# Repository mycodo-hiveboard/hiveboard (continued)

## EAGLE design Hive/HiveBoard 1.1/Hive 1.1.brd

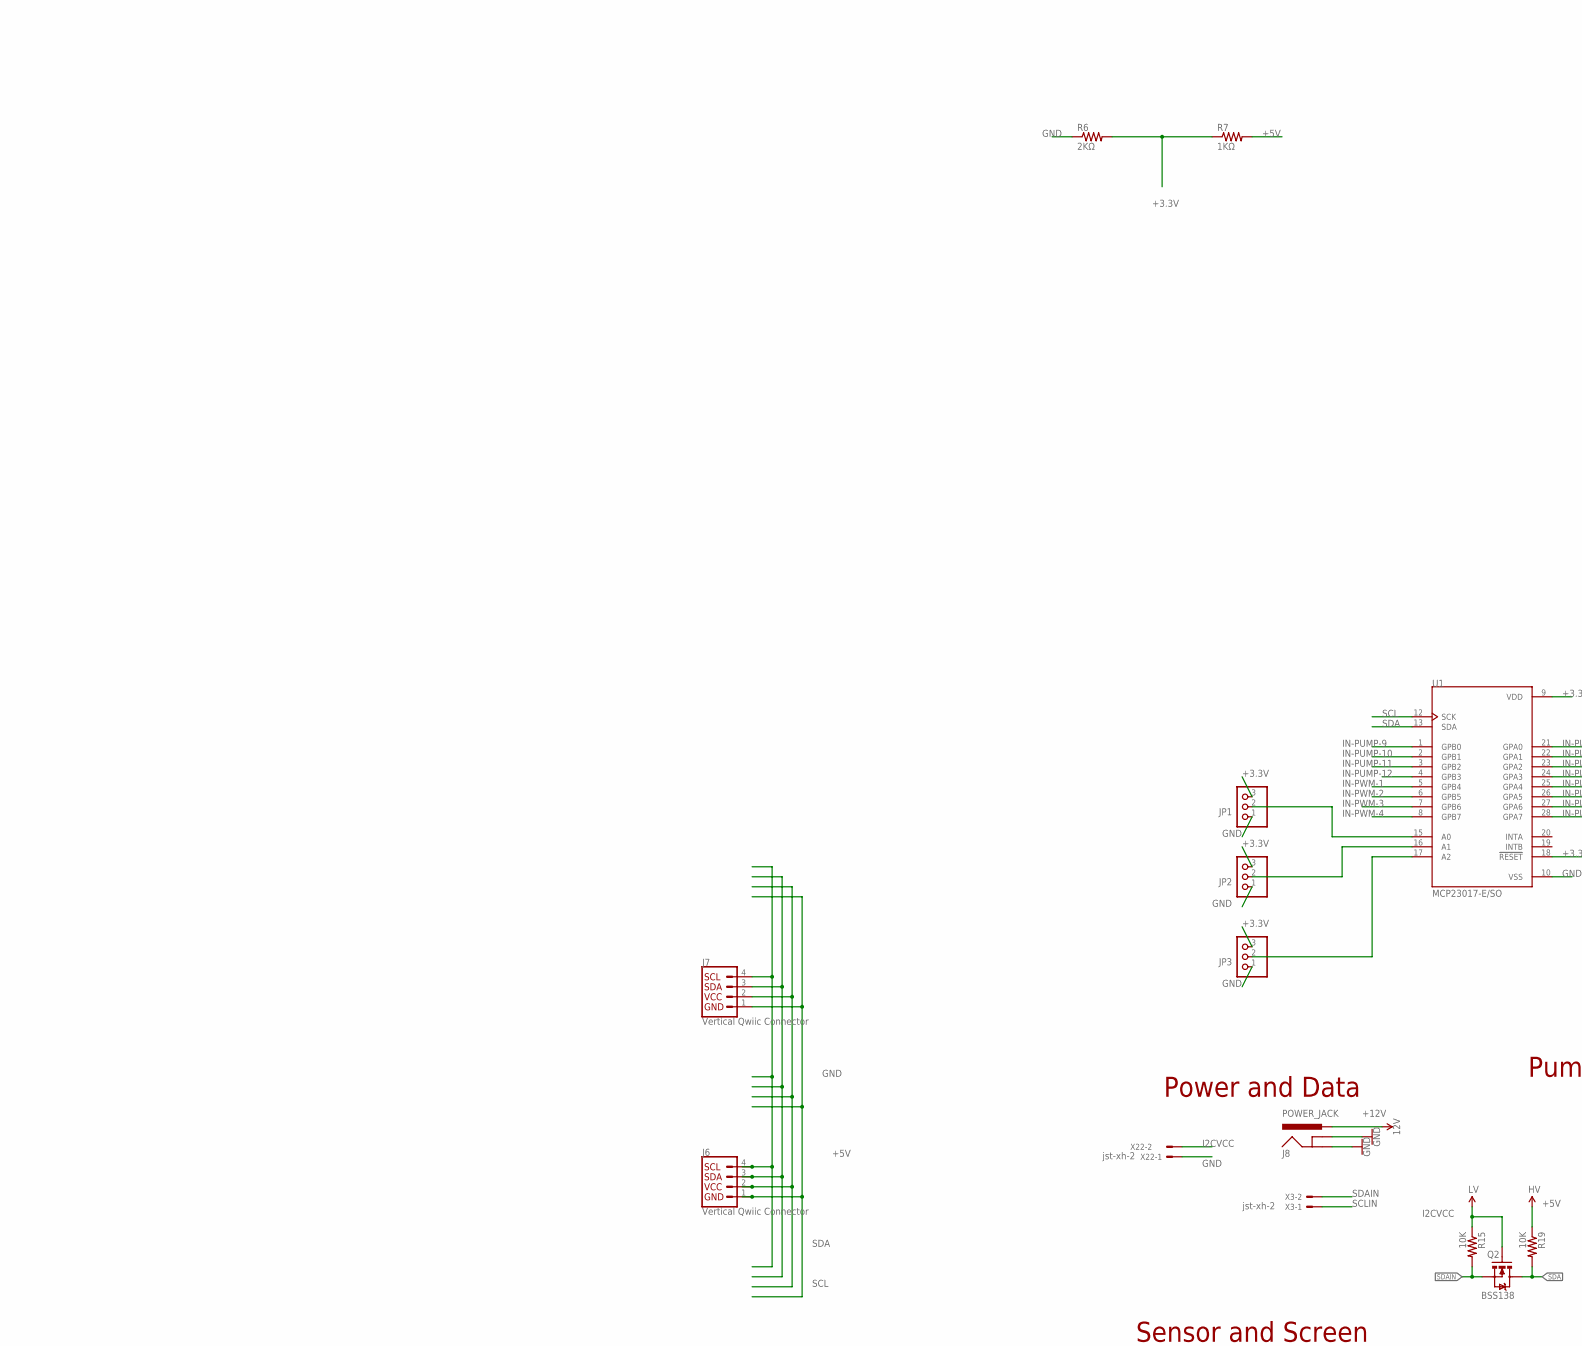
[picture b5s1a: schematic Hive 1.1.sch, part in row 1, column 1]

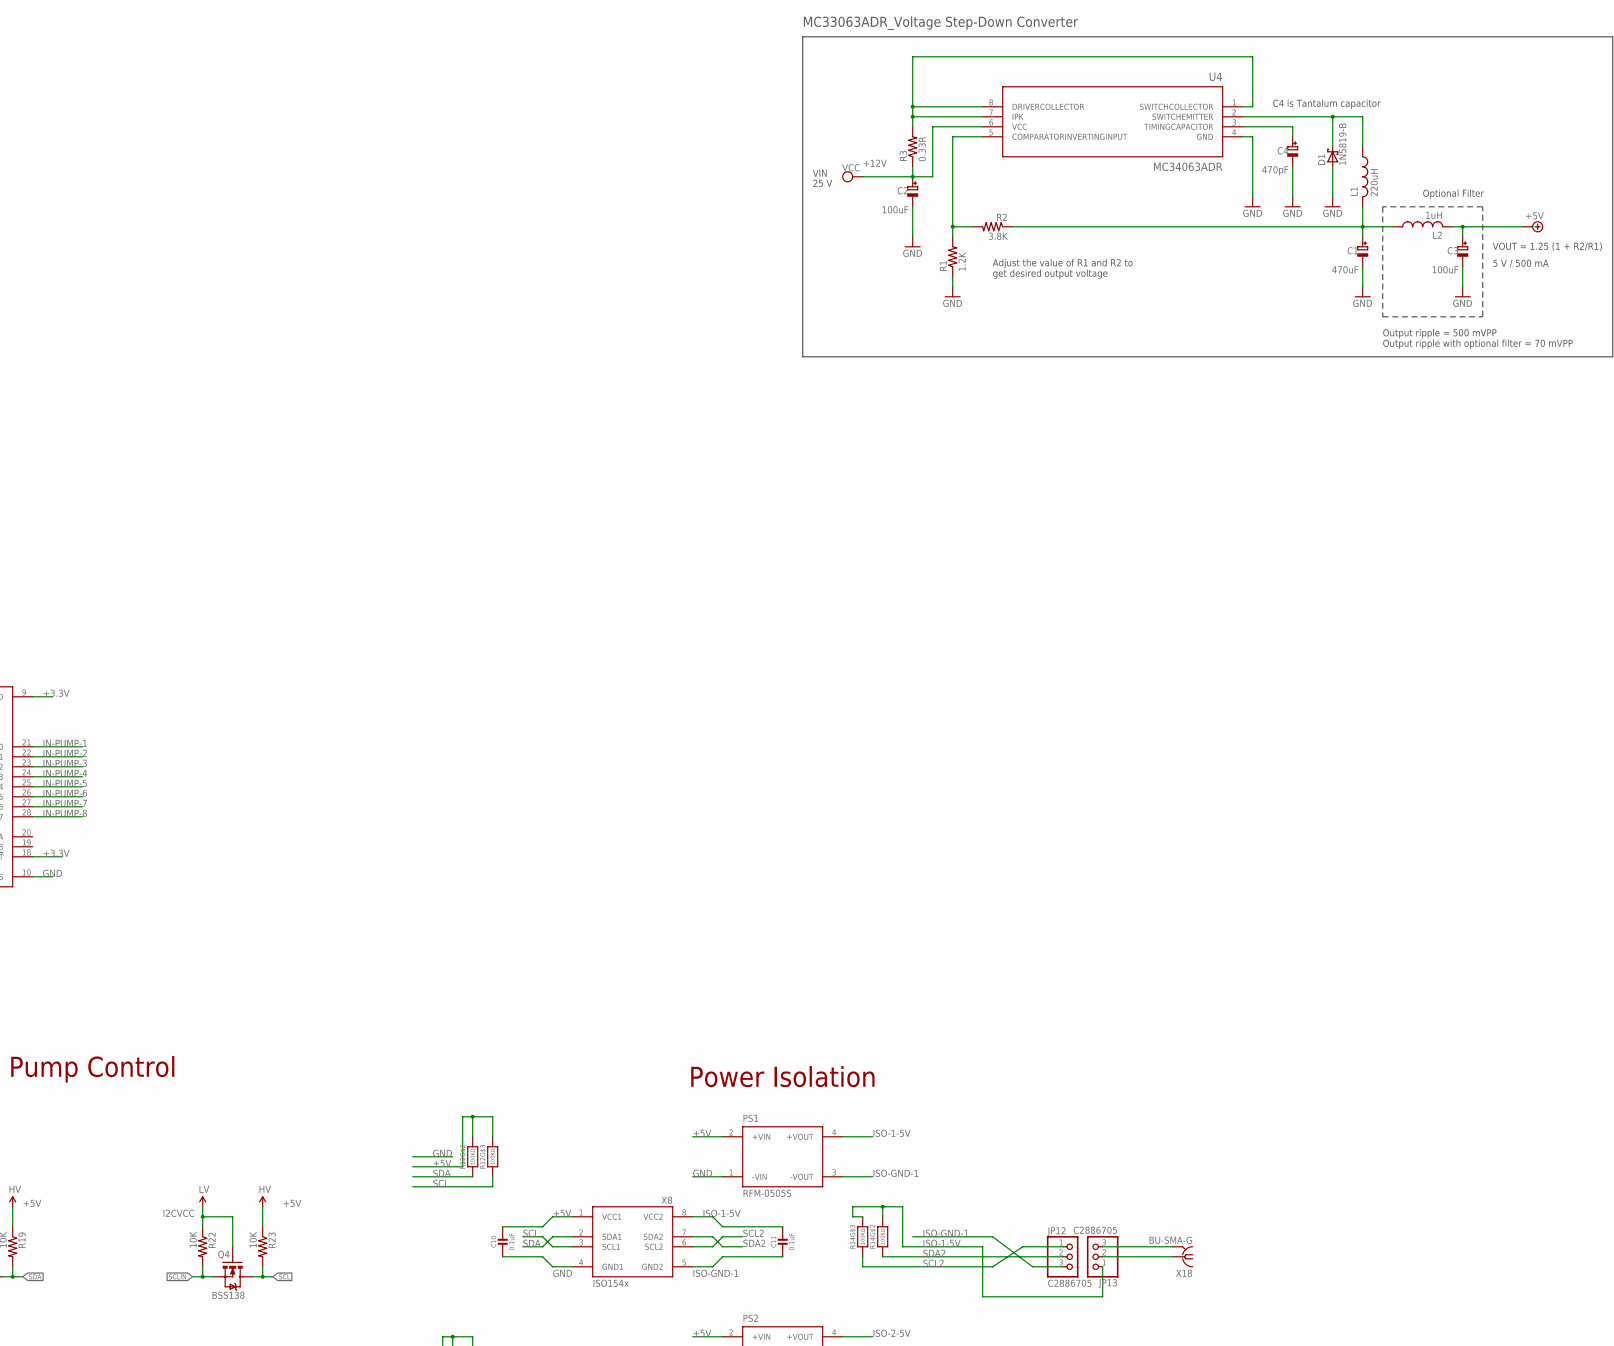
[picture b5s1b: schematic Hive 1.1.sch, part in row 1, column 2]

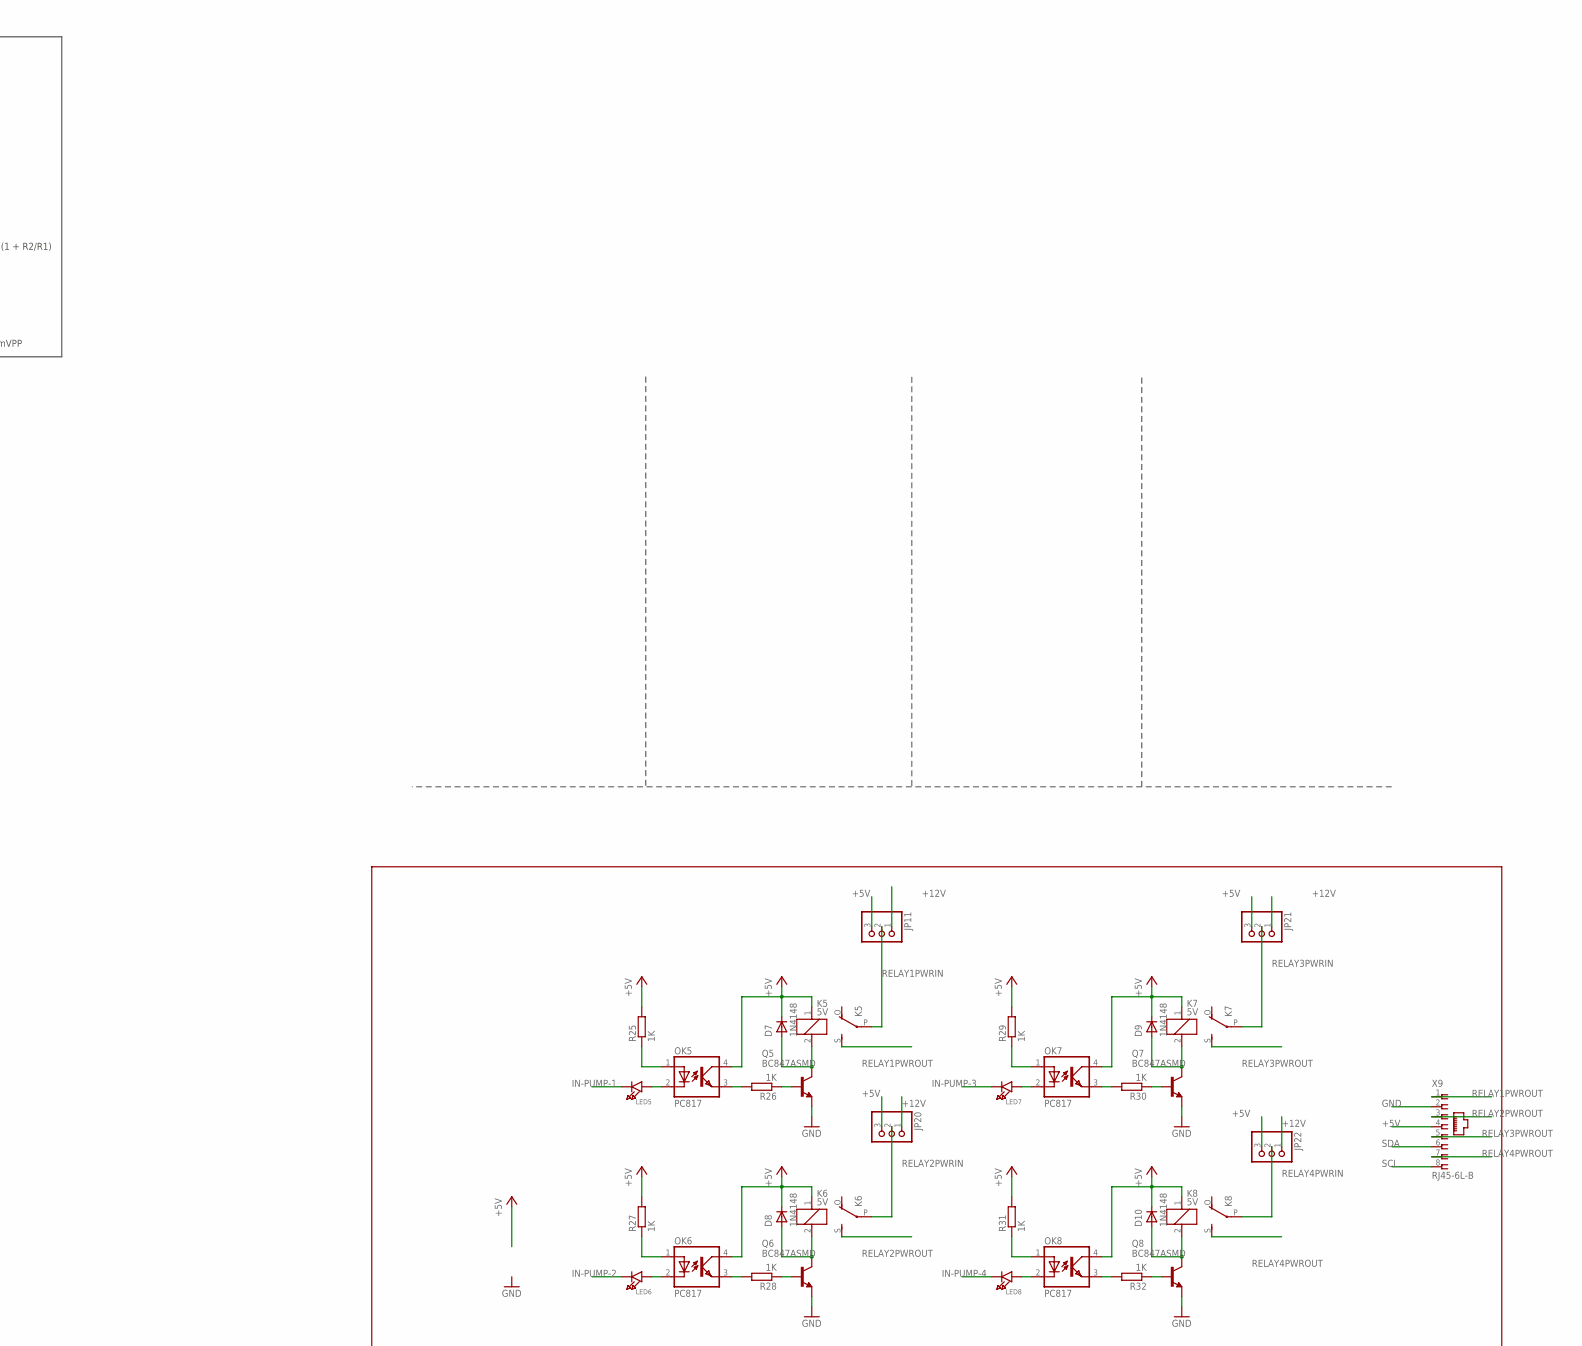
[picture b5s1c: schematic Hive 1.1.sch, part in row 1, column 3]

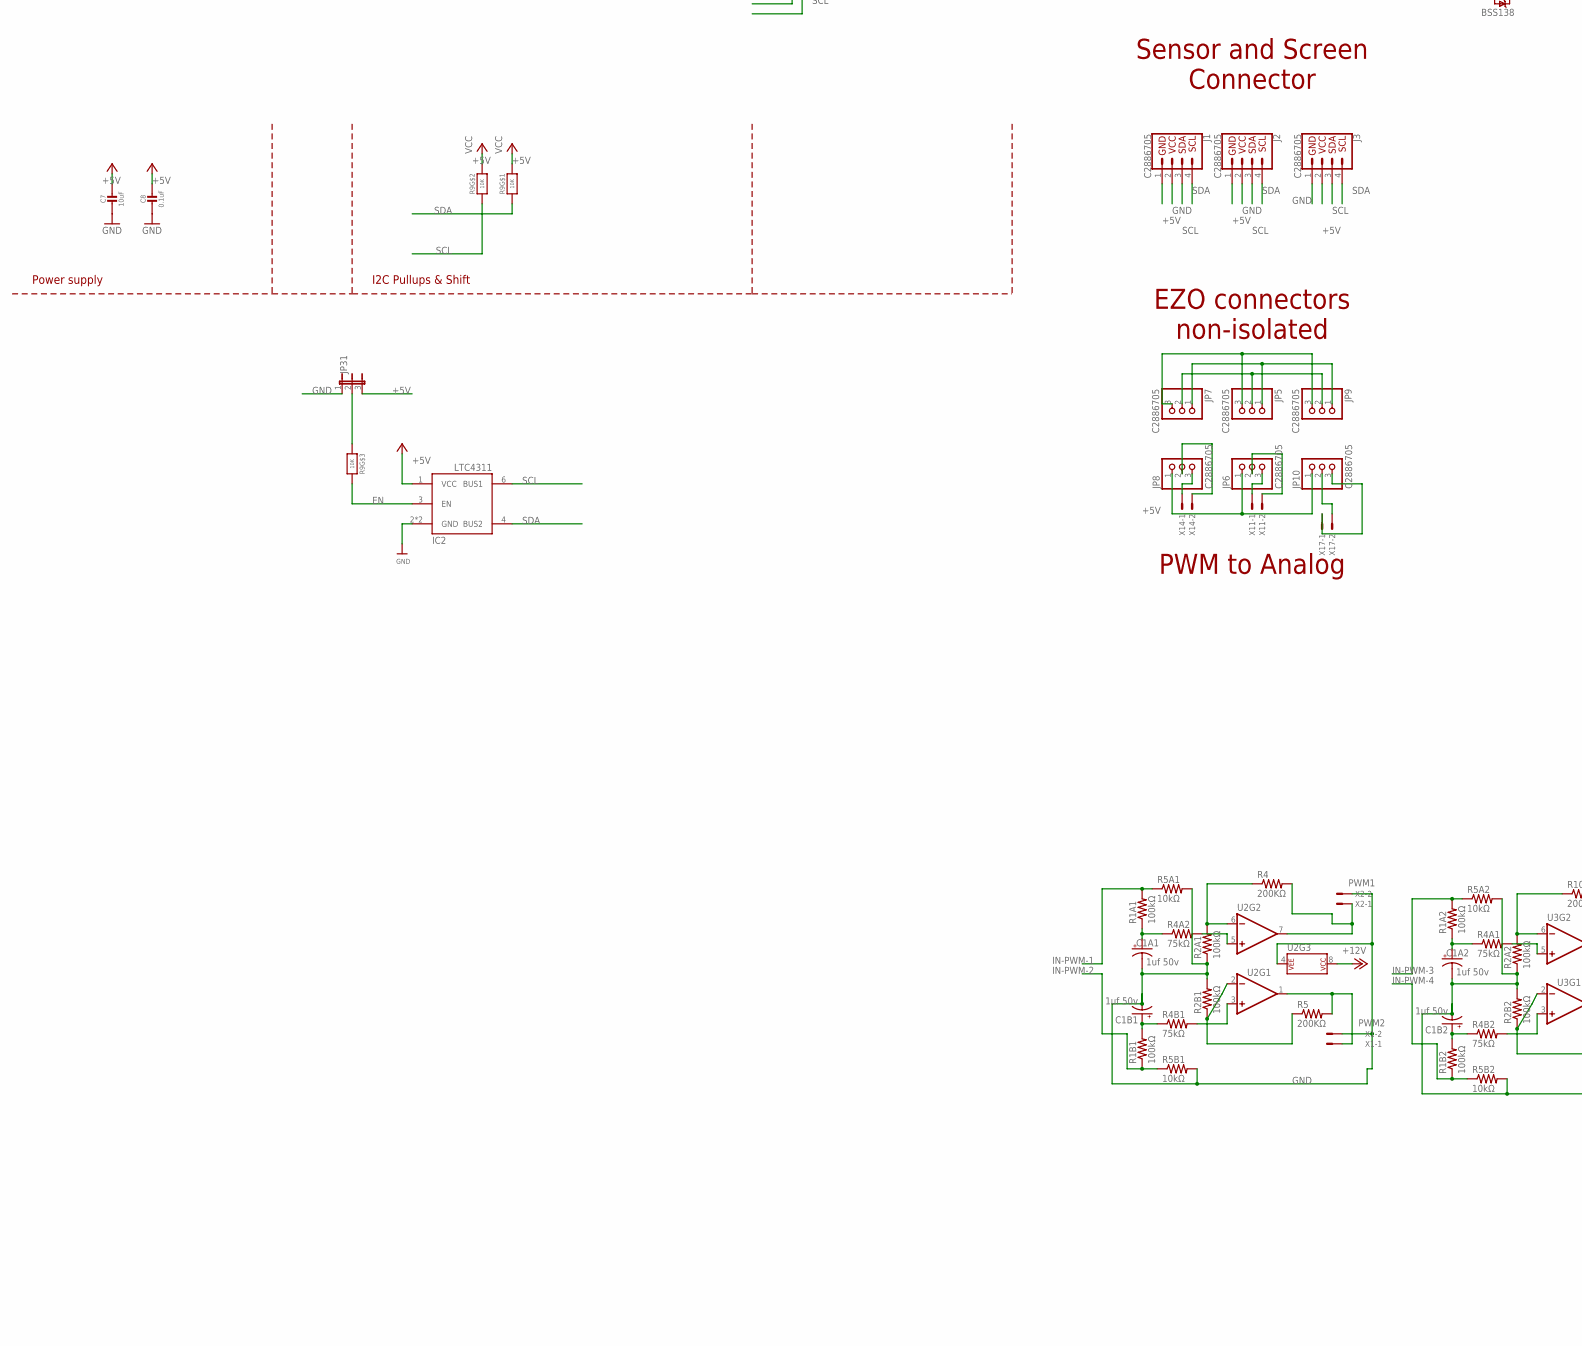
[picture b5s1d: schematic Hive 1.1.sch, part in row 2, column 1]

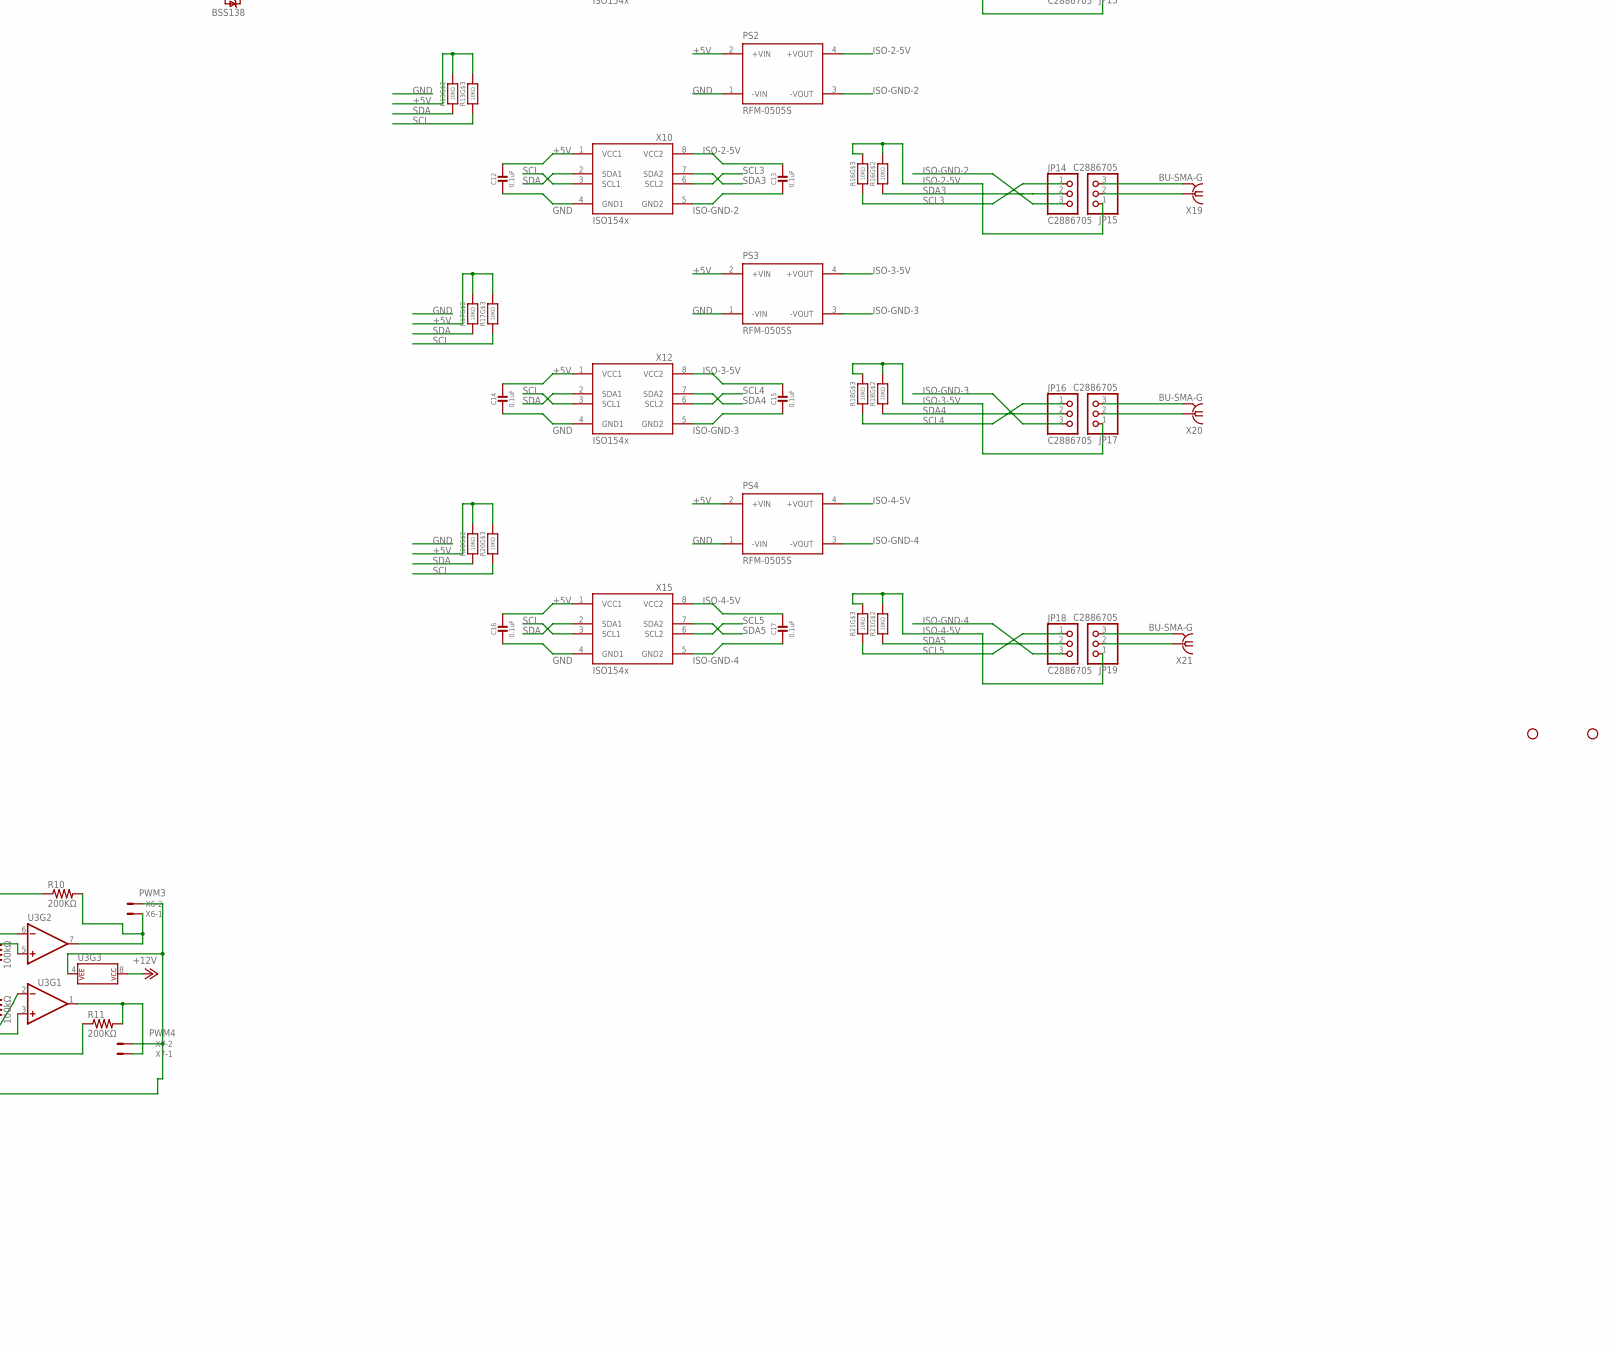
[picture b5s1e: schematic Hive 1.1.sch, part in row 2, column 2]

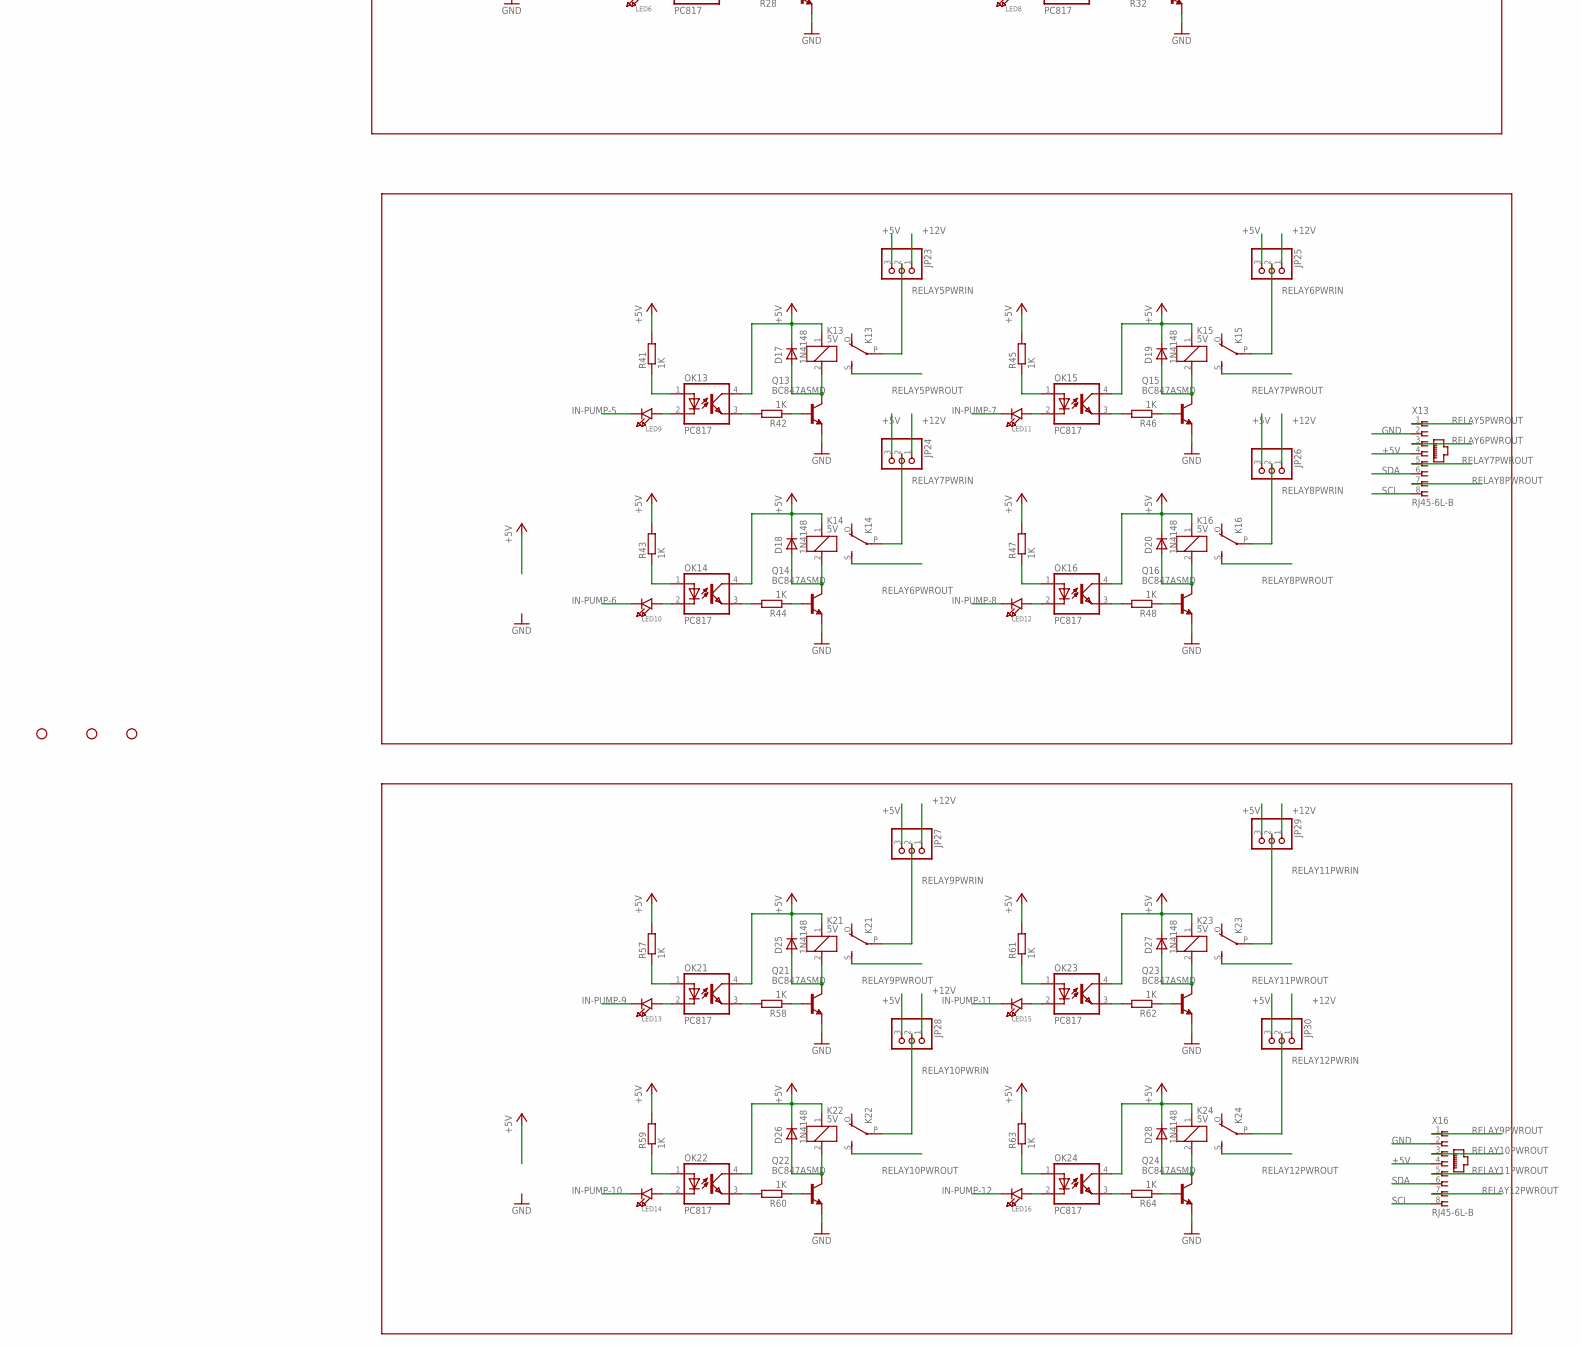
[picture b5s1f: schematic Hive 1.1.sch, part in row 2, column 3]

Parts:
C1: 470uF; PANASONIC_C
C1A1, C1A2, C1B1, C1B2: 1uf 50v; UD-4X5,8_NICHICON
C2, C3: 100uF; PANASONIC_C
C4: 470pF; PANASONIC_C
C7: 10uF; 0805-NO
C8, C10, C11, C12, C13, C14, C15, C16, C17: 0.1uF; 0603-NO
D1: 1N5819-B; DO41-7.6
D7, D8, D9, D10, D17, D18, D19, D20, D25, D26, D27, D28: 1N4148; SMA-DO214AC
H1, H2, H3, H4: STAND-OFF
IC2: LTC4311_SC70; SC70-6L
J1, J2, J3: C2886705; 1X04
J6, J7: Vertical Qwiic Connector; JST04_1MM_VERT
J8: POWER_JACK; POWER_JACK_PTH
JP1, JP2, JP3: HEADER-1X3ROUND; 1X03_ROUND
JP5, JP6, JP7, JP8, JP9, JP10, JP12, JP13, JP14, JP15, JP16, JP17, JP18, JP19: C2886705; 1X03-CLEANBIG
JP11, JP20, JP21, JP22, JP23, JP24, JP25, JP26, JP27, JP28, JP29, JP30: PINHD-1X3; 1X03
JP31: JUMPER3
K5, K6, K7, K8, K13, K14, K15, K16, K21, K22, K23, K24: 5V; ZF112
L1: 220uH; L3216C
L2: 1uH; L3216C
LED5, LED6, LED7, LED8, LED9, LED10, LED11, LED12, LED13, LED14, LED15, LED16: LED0603; CHIPLED_0603
OK5, OK6, OK7, OK8, OK13, OK14, OK15, OK16, OK21, OK22, OK23, OK24: PC817; DIL04
PS1, PS2, PS3, PS4: RFM-0505S; CONV_RFM-0505S
Q2, Q4: BSS138; SOT23-3
Q5, Q6, Q7, Q8, Q13, Q14, Q15, Q16, Q21, Q22, Q23, Q24: BC847ASMD; SOT23
R1: 1.2K; M0805
R1A1, R1A2, R1B1, R1B2, R2A1, R2A2, R2B1, R2B2: 100kΩ; M1206
R2: 3.8K; M0805
R3: 0.33R; M0805
R4, R5, R10, R11: 200KΩ; R0402
R4A1, R4A2, R4B1, R4B2: 75kΩ; M1206
R5A1, R5A2, R5B1, R5B2: 10kΩ; M1206
R6: 2KΩ; R1206
R7: 1KΩ; R1206
R9: 10K; RESPACK_4X0603
R12, R14: 100KΩ; RESPACK_4X0603
R13, R16, R17, R18, R20, R21: 10KΩ; RESPACK_4X0603
R15, R19, R22, R23: 10K; 0603-RES
R25, R26, R27, R28, R29, R30, R31, R32, R41, R42, R43, R44, R45, R46, R47, R48, R57, R58, R59, R60, R61, R62, R63, R64: 1K; R1206
U1: MCP23017-E/SO; SOIC127P1030X265-28N
U2, U3: LM358; SO08
U4: MC34063ADR; D8
X1: PWM2; JST-XH-02-PACKAGE-LONG-PAD
X2: PWM1; JST-XH-02-PACKAGE-LONG-PAD
X3, X11, X14, X17, X22: jst-xh-2; JST-XH-02-PACKAGE-LONG-PAD
X6: PWM3; JST-XH-02-PACKAGE-LONG-PAD
X7: PWM4; JST-XH-02-PACKAGE-LONG-PAD
X8, X10, X12, X15: ISO154X; SOIC8_150MIL
X9, X13, X16: RJ45-6L-B; RJ45-NO-SHIELD
X18, X19, X20, X21: BU-SMA-G

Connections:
+3.3V: JP1.3, JP2.3, JP3.3, R6.2, R7.1, U1.9 (VDD), U1.18 (!RESET)
+5V: C3.+, C7.1, C8.1, C10.1, C12.1, C14.1, C16.1, D7.K (C), D8.K (C), D9.K (C), D10.K (C), D17.K (C), D18.K (C), D19.K (C), D20.K (C), D25.K (C), D26.K (C), D27.K (C), D28.K (C), IC2.1 (VCC), J1.1, J2.1, J3.2, J6.3, J7.3, JP6.1, JP8.1, JP10.1, JP11.3, JP20.3, JP21.3, JP22.3, JP23.3, JP24.3, JP25.3, JP26.3, JP27.3, JP28.3, JP29.3, JP30.3, JP31.3, K5.1, K6.1, K7.1, K8.1, K13.1, K14.1, K15.1, K16.1, K21.1, K22.1, K23.1, K24.1, L2.2, OK5.4 (COL), OK6.4 (COL), OK7.4 (COL), OK8.4 (COL), OK13.4 (COL), OK14.4 (COL), OK15.4 (COL), OK16.4 (COL), OK21.4 (COL), OK22.4 (COL), OK23.4 (COL), OK24.4 (COL), PS1.2 (+VIN), PS2.2 (+VIN), PS3.2 (+VIN), PS4.2 (+VIN), R7.2, R9.7 (2), R9.8 (2), R12.6 (2), R12.7 (2), R13.6 (2), R13.7 (2), R17.6 (2), R17.7 (2), R19.1, R20.6 (2), R20.7 (2), R23.1, R25.2, R27.2, R29.2, R31.2, R41.2, R43.2, R45.2, R47.2, R57.2, R59.2, R61.2, R63.2, X8.1 (VCC1), X9.4, X10.1 (VCC1), X12.1 (VCC1), X13.4, X15.1 (VCC1), X16.4
+12V: C2.+, J8.PWR, JP11.1, JP20.1, JP21.1, JP22.1, JP23.1, JP24.1, JP25.1, JP26.1, JP27.1, JP28.1, JP29.1, JP30.1, R3.1, U2.8 (P$V+), U3.8 (P$V+), U4.6 (VCC)
EN: IC2.3 (EN), R9.6 (2)
GND: C1.-, C1A1.-, C1A2.-, C1B1.-, C1B2.-, C2.-, C3.-, C4.-, C7.2, C8.2, C10.2, C12.2, C14.2, C16.2, D1.A, IC2.2 (GND), IC2.5 (GND), J1.2, J2.2, J3.1, J6.4, J7.4, J8.GND, J8.GNDBREAK, JP1.1, JP2.1, JP3.1, JP5.3, JP7.3, JP9.3, JP31.1, PS1.1 (-VIN), PS2.1 (-VIN), PS3.1 (-VIN), PS4.1 (-VIN), Q5.2 (E), Q6.2 (E), Q7.2 (E), Q8.2 (E), Q13.2 (E), Q14.2 (E), Q15.2 (E), Q16.2 (E), Q21.2 (E), Q22.2 (E), Q23.2 (E), Q24.2 (E), R1.1, R2A1.1, R2A2.1, R2B1.2, R2B2.2, R5A1.2, R5A2.2, R5B1.2, R5B2.2, R6.1, U1.10 (VSS), U2.4 (P$V-), U3.4 (P$V-), U4.4 (GND), X1.2, X2.2, X6.2, X7.2, X8.4 (GND1), X9.2, X10.4 (GND1), X12.4 (GND1), X13.2, X15.4 (GND1), X16.2, X22.1
I2CVCC: Q2.1 (G), Q4.1 (G), R15.1, R22.1, X22.2
IN-PUMP-1: LED5.C, U1.21 (GPA0)
IN-PUMP-2: LED6.C, U1.22 (GPA1)
IN-PUMP-3: LED7.C, U1.23 (GPA2)
IN-PUMP-4: LED8.C, U1.24 (GPA3)
IN-PUMP-5: LED9.C, U1.25 (GPA4)
IN-PUMP-6: LED10.C, U1.26 (GPA5)
IN-PUMP-7: LED11.C, U1.27 (GPA6)
IN-PUMP-8: LED12.C, U1.28 (GPA7)
IN-PUMP-9: LED13.C, U1.1 (GPB0)
IN-PUMP-10: LED14.C, U1.2 (GPB1)
IN-PUMP-11: LED15.C, U1.3 (GPB2)
IN-PUMP-12: LED16.C, U1.4 (GPB3)
IN-PWM-1: R1A1.2, R5A1.1, U1.5 (GPB4)
IN-PWM-2: R1B1.1, R5B1.1, U1.6 (GPB5)
IN-PWM-3: R1A2.2, R5A2.1, U1.7 (GPB6)
IN-PWM-4: R1B2.1, R5B2.1, U1.8 (GPB7)
ISO-1-5V: C11.1, JP13.1, PS1.4 (+VOUT), R14.6 (2), R14.7 (2), X8.8 (VCC2)
ISO-2-5V: C13.1, JP15.1, PS2.4 (+VOUT), R16.6 (2), R16.7 (2), X10.8 (VCC2)
ISO-3-5V: C15.1, JP17.1, PS3.4 (+VOUT), R18.6 (2), R18.7 (2), X12.8 (VCC2)
ISO-4-5V: C17.1, JP19.1, PS4.4 (+VOUT), R21.6 (2), R21.7 (2), X15.8 (VCC2)
ISO-GND-1: C11.2, JP12.3, PS1.3 (-VOUT), X8.5 (GND2)
ISO-GND-2: C13.2, JP14.3, PS2.3 (-VOUT), X10.5 (GND2)
ISO-GND-3: C15.2, JP16.3, PS3.3 (-VOUT), X12.5 (GND2)
ISO-GND-4: C17.2, JP18.3, PS4.3 (-VOUT), X15.5 (GND2)
ISO-PRB-1+: JP13.2, X18.1
ISO-PRB-1GND: JP13.3, X18.2, X18.3 (2), X18.4 (2), X18.5 (2)
ISO-PRB-2+: JP15.2, X19.1
ISO-PRB-2GND: JP15.3, X19.2, X19.3 (2), X19.4 (2), X19.5 (2)
ISO-PRB-3+: JP17.2, X20.1
ISO-PRB-3GND: JP17.3, X20.2, X20.3 (2), X20.4 (2), X20.5 (2)
ISO-PRB-4+: JP19.2, X21.1
ISO-PRB-4GND: JP19.3, X21.2, X21.3 (2), X21.4 (2), X21.5 (2)
unnamed: C1A1.+, R1A1.1, R4A2.1
unnamed: D1.C, JP31.2, L1.1, R9.3 (1), U4.2 (SWITCHEMITTER)
unnamed: C1.+, L1.2, L2.1, R2.1
unnamed: C4.+, U4.3 (TIMINGCAPACITOR)
unnamed: C1B1.+, R1B1.2, R4B1.1
unnamed: R2A1.2, R4.1, U2.6 (-IN)
unnamed: R1.2, R2.2, U4.5 (COMPARATORINVERTINGINPUT)
unnamed: R2B1.1, R5.1, U2.2 (-IN)
unnamed: R3.2, U4.1 (SWITCHCOLLECTOR), U4.7 (IPK), U4.8 (DRIVERCOLLECTOR)
unnamed: R4A2.2, U2.5 (+IN)
unnamed: R4B1.2, U2.3 (+IN)
unnamed: C1A2.+, R1A2.1, R4A1.1
unnamed: C1B2.+, R1B2.2, R4B2.1
unnamed: R2A2.2, R10.1, U3.6 (-IN)
unnamed: R2B2.1, R11.1, U3.2 (-IN)
unnamed: R4A1.2, U3.5 (+IN)
unnamed: R4B2.2, U3.3 (+IN)
unnamed: JP1.2, U1.15 (A0)
unnamed: JP2.2, U1.16 (A1)
unnamed: JP3.2, U1.17 (A2)
unnamed: LED5.A, OK5.2 (C)
unnamed: OK5.1 (A), R25.1
unnamed: OK5.3 (EMIT), R26.2
unnamed: D7.A, K5.2, Q5.3 (C)
unnamed: Q5.1 (B), R26.1
unnamed: LED6.A, OK6.2 (C)
unnamed: OK6.1 (A), R27.1
unnamed: OK6.3 (EMIT), R28.2
unnamed: D8.A, K6.2, Q6.3 (C)
unnamed: Q6.1 (B), R28.1
unnamed: LED7.A, OK7.2 (C)
unnamed: OK7.1 (A), R29.1
unnamed: OK7.3 (EMIT), R30.2
unnamed: D9.A, K7.2, Q7.3 (C)
unnamed: Q7.1 (B), R30.1
unnamed: LED8.A, OK8.2 (C)
unnamed: OK8.1 (A), R31.1
unnamed: OK8.3 (EMIT), R32.2
unnamed: D10.A, K8.2, Q8.3 (C)
unnamed: Q8.1 (B), R32.1
unnamed: LED9.A, OK13.2 (C)
unnamed: OK13.1 (A), R41.1
unnamed: OK13.3 (EMIT), R42.2
unnamed: D17.A, K13.2, Q13.3 (C)
unnamed: Q13.1 (B), R42.1
unnamed: LED10.A, OK14.2 (C)
unnamed: OK14.1 (A), R43.1
unnamed: OK14.3 (EMIT), R44.2
unnamed: D18.A, K14.2, Q14.3 (C)
unnamed: Q14.1 (B), R44.1
unnamed: LED11.A, OK15.2 (C)
unnamed: OK15.1 (A), R45.1
unnamed: OK15.3 (EMIT), R46.2
unnamed: D19.A, K15.2, Q15.3 (C)
unnamed: Q15.1 (B), R46.1
unnamed: LED12.A, OK16.2 (C)
unnamed: OK16.1 (A), R47.1
unnamed: OK16.3 (EMIT), R48.2
unnamed: D20.A, K16.2, Q16.3 (C)
unnamed: Q16.1 (B), R48.1
unnamed: LED13.A, OK21.2 (C)
unnamed: OK21.1 (A), R57.1
unnamed: OK21.3 (EMIT), R58.2
unnamed: D25.A, K21.2, Q21.3 (C)
unnamed: Q21.1 (B), R58.1
unnamed: LED14.A, OK22.2 (C)
unnamed: OK22.1 (A), R59.1
unnamed: OK22.3 (EMIT), R60.2
unnamed: D26.A, K22.2, Q22.3 (C)
unnamed: Q22.1 (B), R60.1
unnamed: LED15.A, OK23.2 (C)
unnamed: OK23.1 (A), R61.1
unnamed: OK23.3 (EMIT), R62.2
unnamed: D27.A, K23.2, Q23.3 (C)
unnamed: Q23.1 (B), R62.1
unnamed: LED16.A, OK24.2 (C)
unnamed: OK24.1 (A), R63.1
unnamed: OK24.3 (EMIT), R64.2
unnamed: D28.A, K24.2, Q24.3 (C)
unnamed: Q24.1 (B), R64.1
NISO-PRB-1+: JP6.2, X11.2
NISO-PRB-1GND: JP6.3, X11.1
NISO-PRB-2+: JP8.2, X14.2
NISO-PRB-2GND: JP8.3, X14.1
NISO-PRB-3+: JP10.2, X17.2
NISO-PRB-3GND: JP10.3, X17.1
PWM-OUT-1: R4.2, U2.7 (OUT), X2.1
PWM-OUT-2: R5.2, U2.1 (OUT), X1.1
PWM-OUT-3: R10.2, U3.7 (OUT), X6.1
PWM-OUT-4: R11.2, U3.1 (OUT), X7.1
RELAY1PWRIN: JP11.2, K5.P
RELAY1PWROUT: K5.S, X9.1
RELAY2PWRIN: JP20.2, K6.P
RELAY2PWROUT: K6.S, X9.3
RELAY3PWRIN: JP21.2, K7.P
RELAY3PWROUT: K7.S, X9.5
RELAY4PWRIN: JP22.2, K8.P
RELAY4PWROUT: K8.S, X9.7
RELAY5PWRIN: JP23.2, K13.P
RELAY5PWROUT: K13.S, X13.1
RELAY6PWRIN: JP25.2, K15.P
RELAY6PWROUT: K14.S, X13.3
RELAY7PWRIN: JP24.2, K14.P
RELAY7PWROUT: K15.S, X13.5
RELAY8PWRIN: JP26.2, K16.P
RELAY8PWROUT: K16.S, X13.7
RELAY9PWRIN: JP27.2, K21.P
RELAY9PWROUT: K21.S, X16.1
RELAY10PWRIN: JP28.2, K22.P
RELAY10PWROUT: K22.S, X16.3
RELAY11PWRIN: JP29.2, K23.P
RELAY11PWROUT: K23.S, X16.5
RELAY12PWRIN: JP30.2, K24.P
RELAY12PWROUT: K24.S, X16.7
SCL: IC2.6 (BUS1), J1.3, J2.3, J3.3, J6.1, J7.1, JP5.1, JP7.1, JP9.1, Q4.3 (D), R9.2 (1), R12.3 (1), R13.3 (1), R17.3 (1), R20.3 (1), R23.2, U1.12 (SCK), X8.3 (SCL1), X9.8, X10.3 (SCL1), X12.3 (SCL1), X13.8, X15.3 (SCL1), X16.8
SCL2: JP12.1, R14.3 (1), X8.6 (SCL2)
SCL3: JP14.1, R16.3 (1), X10.6 (SCL2)
SCL4: JP16.1, R18.3 (1), X12.6 (SCL2)
SCL5: JP18.1, R21.3 (1), X15.6 (SCL2)
SCLIN: Q4.2 (S), R22.2, X3.1
SDA: IC2.4 (BUS2), J1.4, J2.4, J3.4, J6.2, J7.2, JP5.2, JP7.2, JP9.2, Q2.3 (D), R9.1, R12.2 (1), R13.2 (1), R17.2 (1), R19.2, R20.2 (1), U1.13 (SDA), X8.2 (SDA1), X9.6, X10.2 (SDA1), X12.2 (SDA1), X13.6, X15.2 (SDA1), X16.6
SDA2: JP12.2, R14.2 (1), X8.7 (SDA2)
SDA3: JP14.2, R16.2 (1), X10.7 (SDA2)
SDA4: JP16.2, R18.2 (1), X12.7 (SDA2)
SDA5: JP18.2, R21.2 (1), X15.7 (SDA2)
SDAIN: Q2.2 (S), R15.2, X3.2

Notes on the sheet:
Power Isolation
Pump Control
PWM to Analog
EZO connectors non-isolated
Sensor and Screen Connector
Power and Data
25 V
5 V / 500 mA
Optional Filter
VOUT = 1.25 (1 + R2/R1)
MC33063ADR_Voltage Step-Down Converter
VIN
Adjust the value of R1 and R2 to get desired output voltage
Output ripple = 500 mVPP Output ripple with optional filter = 70 mVPP
C4 is Tantalum capacitor
I2C Pullups & Shift
Power supply

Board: 4 copper layers, 214 parts (0 on the bottom side), 164 nets, no tracks yet.
